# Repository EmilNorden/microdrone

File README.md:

# microdrone

## Controller dev kit

ESP32-S3-Wroom-1-n8r8\
Datasheet: https://www.espressif.com/sites/default/files/documentation/esp32-s3-wroom-1_wroom-1u_datasheet_en.pdf \
Hardware ref: https://docs.espressif.com/projects/esp-dev-kits/en/latest/esp32s3/esp32-s3-devkitc-1/user_guide_v1.1.html#hardware-reference \
Power: 3.0-3.6V\
Rust dev on ESP32: https://docs.espressif.com/projects/rust/book/

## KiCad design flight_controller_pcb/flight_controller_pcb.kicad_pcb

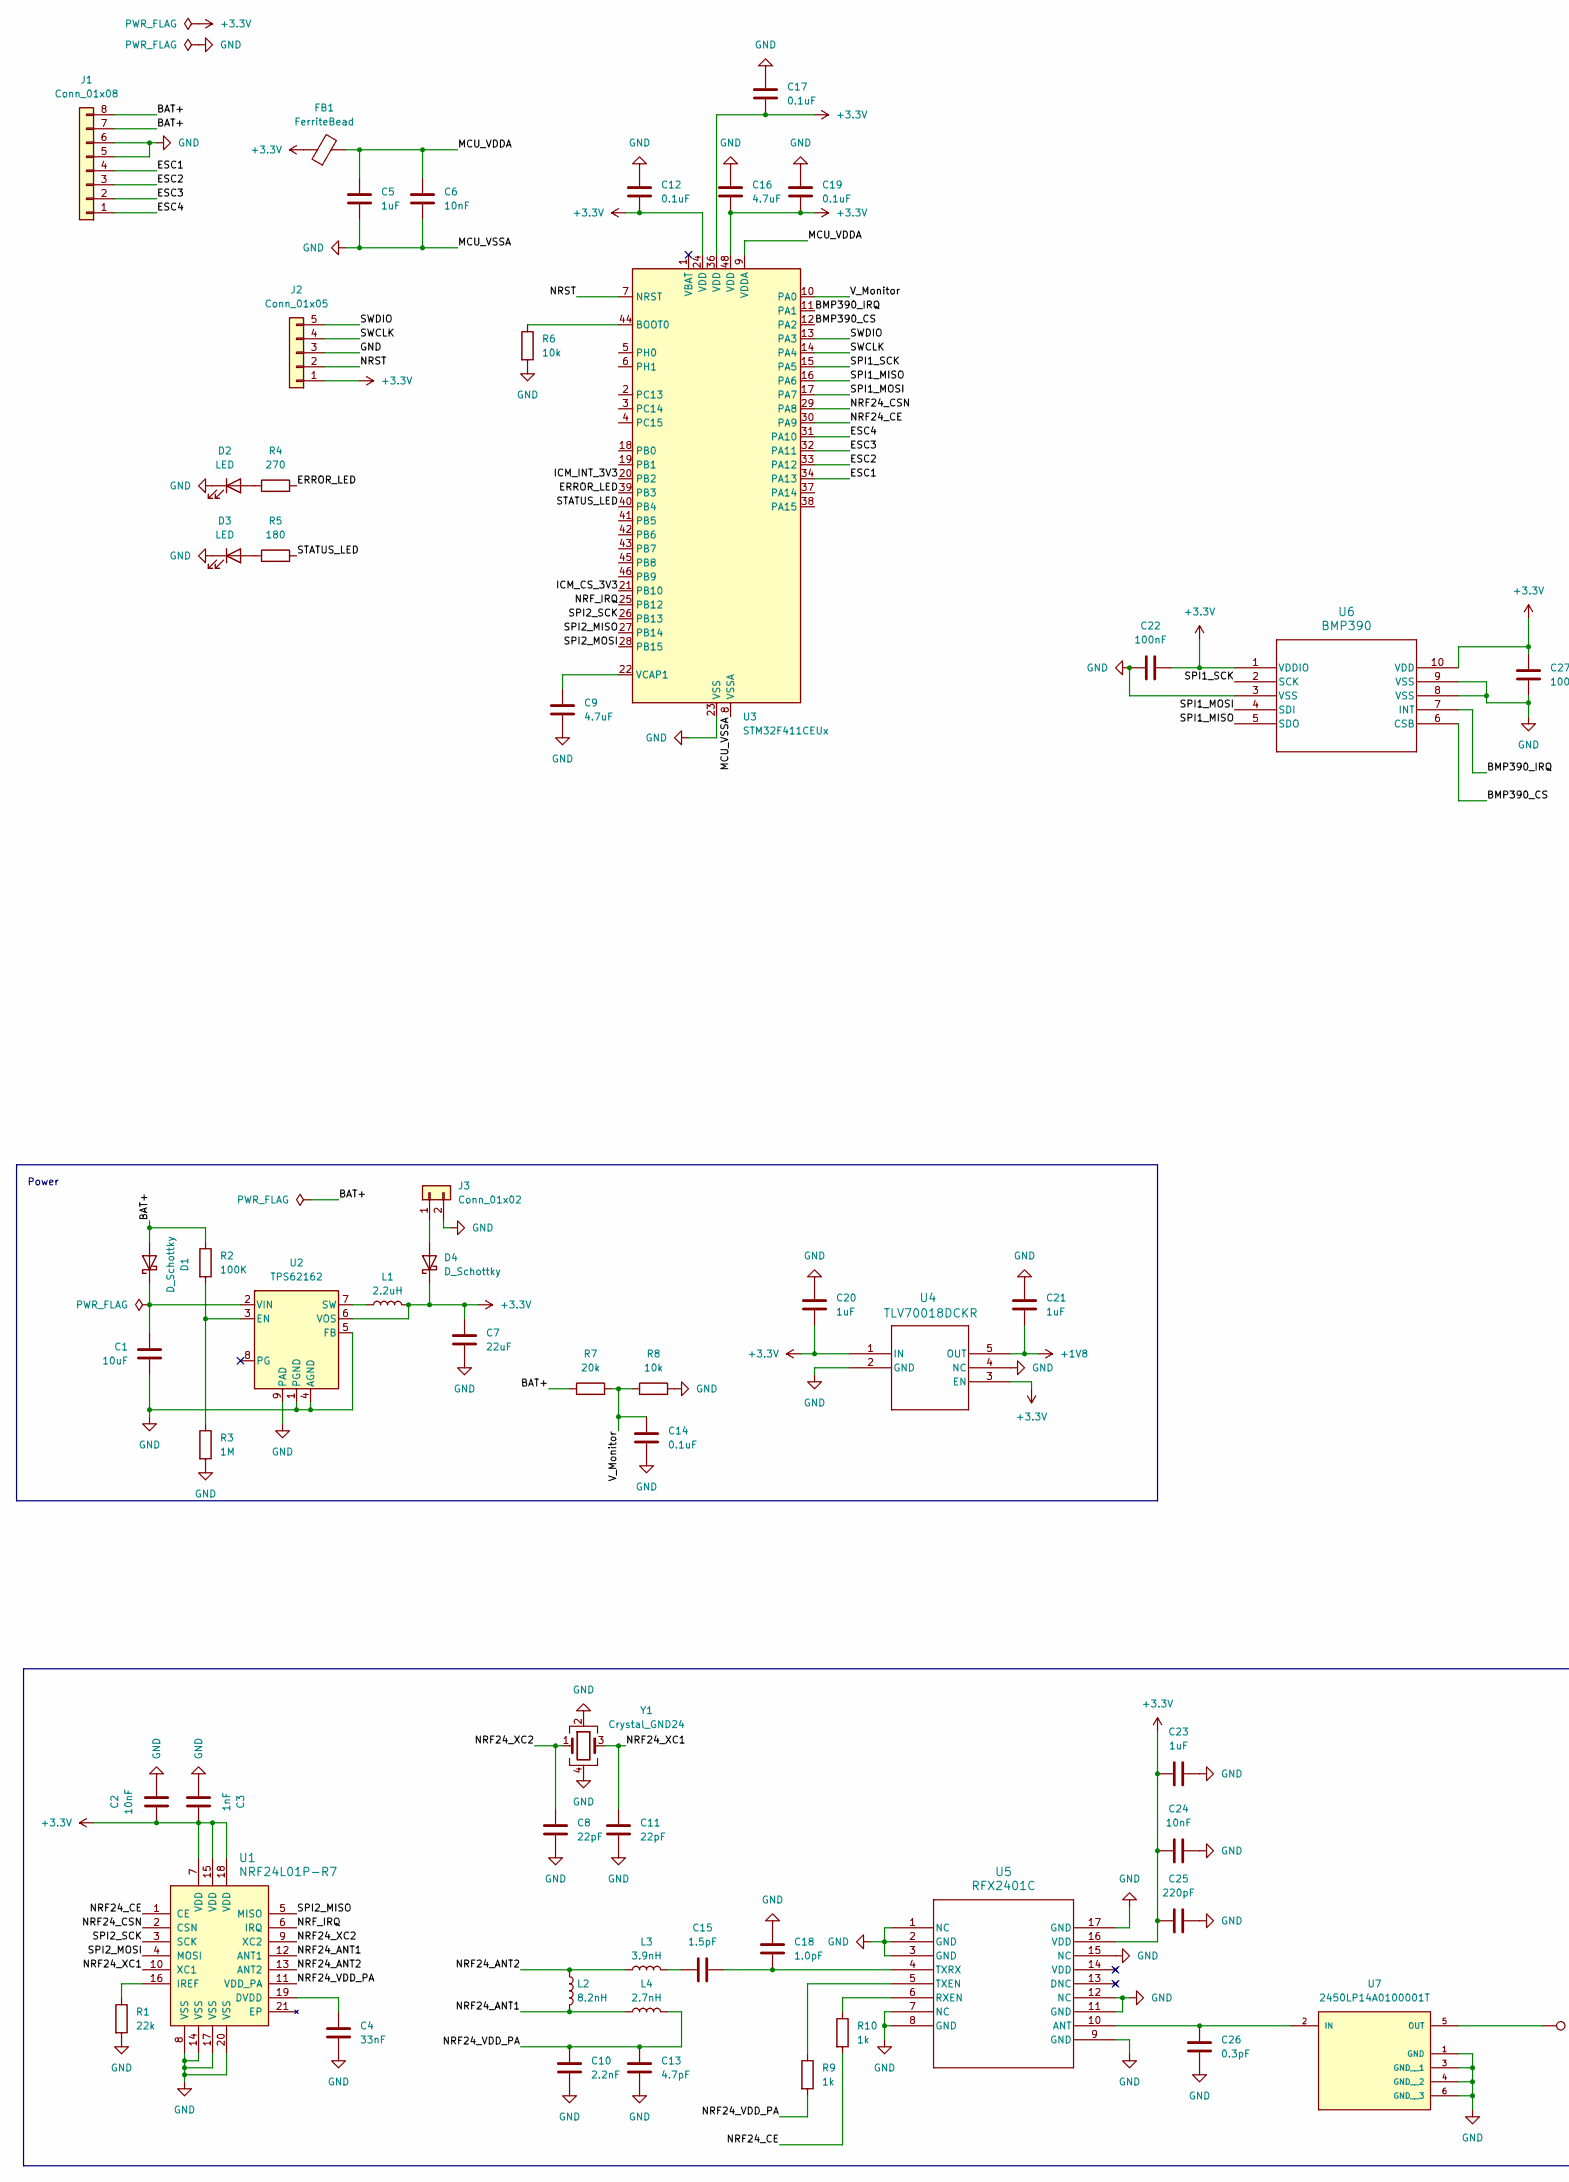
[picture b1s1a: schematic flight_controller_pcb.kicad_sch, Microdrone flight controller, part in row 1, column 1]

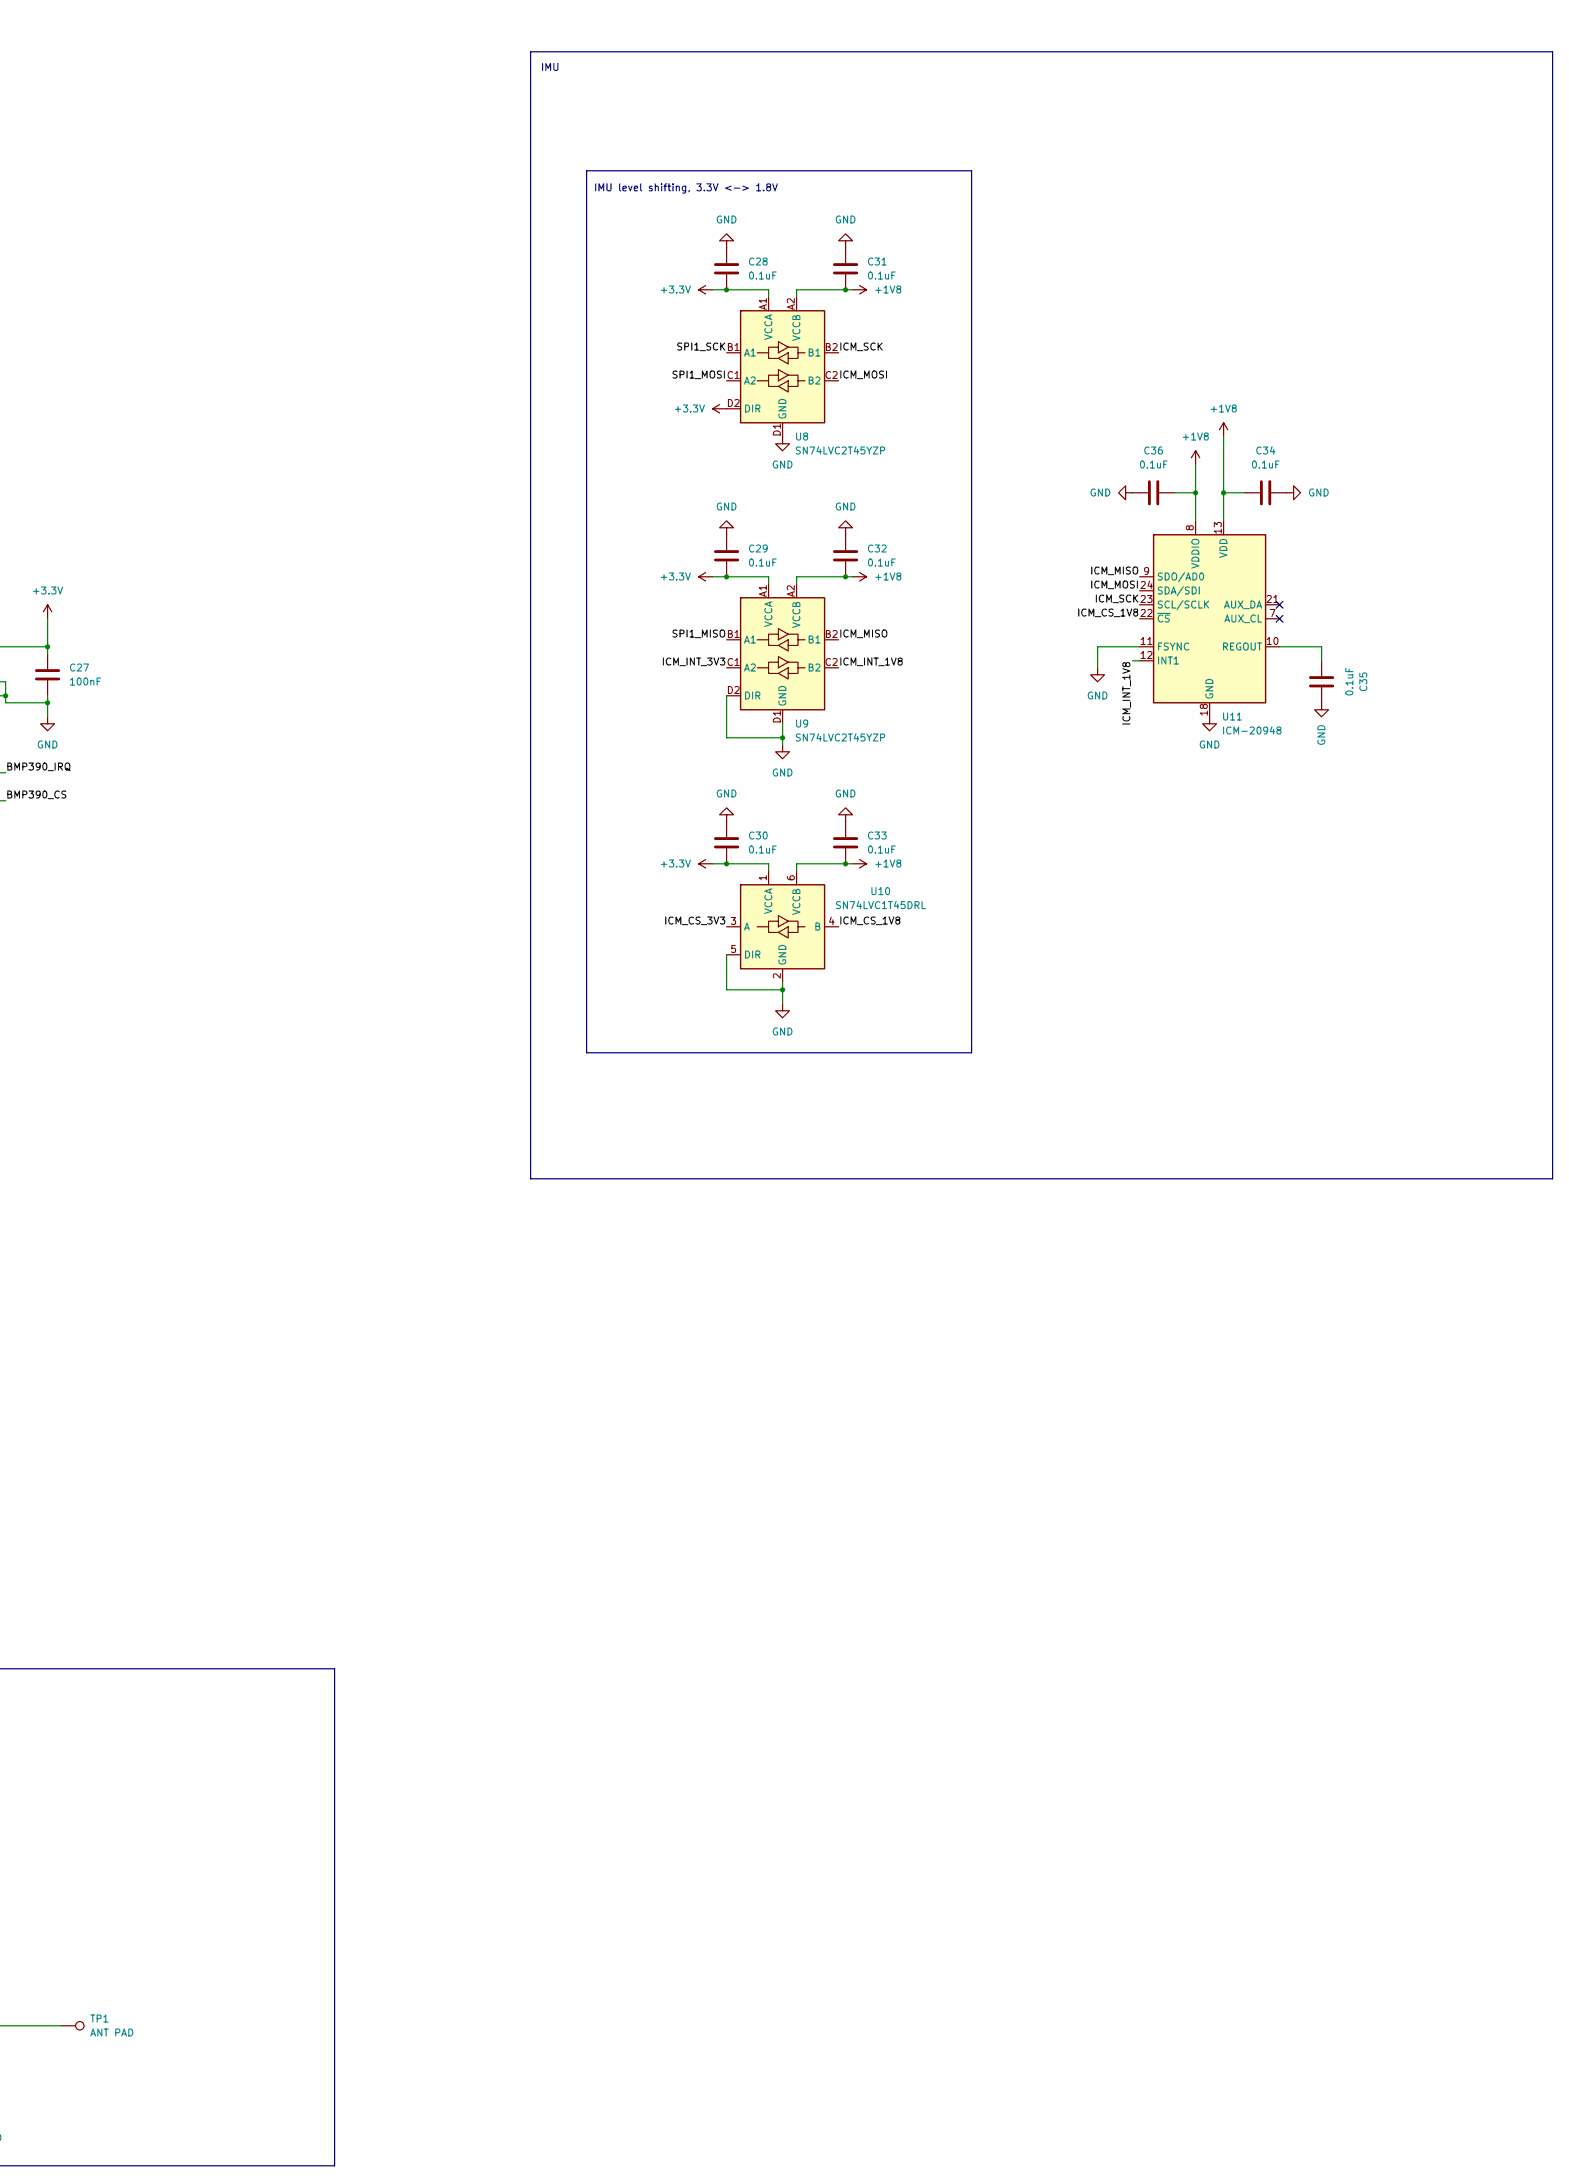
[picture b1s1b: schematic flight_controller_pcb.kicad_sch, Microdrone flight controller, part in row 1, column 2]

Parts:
C1: 10uF; C_0603_1608Metric
C2, C6: 10nF; C_0402_1005Metric
C3: 1nF; C_0402_1005Metric
C4: 33nF; C_0402_1005Metric
C5, C20, C21, C23: 1uF; C_0402_1005Metric
C7: 22uF; C_0805_2012Metric
C8, C11: 22pF; C_0402_1005Metric
C9: 4.7uF; C_0603_1608Metric
C10: 2.2nF; C_0402_1005Metric
C12, C14, C17, C19, C28, C29, C30, C31, C32, C33: 0.1uF; C_0402_1005Metric
C13: 4.7pF; C_0402_1005Metric
C15: 1.5pF; C_0402_1005Metric
C16: 4.7uF; C_0603_1608Metric; LCSC C107368
C18: 1.0pF; C_0402_1005Metric
C22, C27: 100nF; C_0402_1005Metric
C24: 10nF; C_0603_1608Metric
C25: 220pF; C_0402_1005Metric
C26: 0.3pF; C_0201_0603Metric
C34, C35, C36: 0.1uF; C_0402_1005Metric; LCSC C1525
D1: D_Schottky; D_SOD-323
D2, D3: LED; LED_0402_1005Metric
D4: D_Schottky; Diode_SMD_SOD-723
FB1: FerriteBead; L_0603_1608Metric; LCSC C1002
J1: Conn_01x08; JST_SH_ZX-SH1.0-8PWT; LCSC C7430450
J2: Conn_01x05; PinHeader_1x05_P2.54mm_Horizontal
J3: Conn_01x02; PinHeader_1x02_P2.54mm_Horizontal
L1: 2.2uH; Inductor_Coilcraft_XFL3012-222MEC
L2: 8.2nH; L_0201_0603Metric
L3: 3.9nH; L_0201_0603Metric
L4: 2.7nH; L_0201_0603Metric
R1: 22k; R_0402_1005Metric
R2: 100K; R_0402_1005Metric
R3: 1M; R_0402_1005Metric
R4: 270; R_0402_1005Metric
R5: 180; R_0402_1005Metric
R6, R8: 10k; R_0402_1005Metric
R7: 20k; R_0402_1005Metric
R9, R10: 1k; R_0402_1005Metric
TP1: ANT PAD; TestPoint_Pad_3.0x3.0mm
U1: NRF24L01P-R7; QFN-20-1EP_4x4mm_RevA; MPN NRF24L01P-R7; Digi-Key_PN 1490-1033-1-ND
U2: TPS62162; WSON-8-1EP_2x2mm_P0.5mm_EP0.9x1.6mm_ThermalVias
U3: STM32F411CEUx; QFN-48-1EP_7x7mm_P0.5mm_EP5.6x5.6mm
U4: TLV70018DCKR; DCK5
U5: RFX2401C; RFX2401C_SKY
U6: BMP390; 10LGA_2X2X0p75_BOS
U7: 2450LP14A0100001T; ICCAF50P160X80X70-6N; PARTREV 06/23/03
U8, U9: SN74LVC2T45YZP; Texas_DSBGA-8_0.9x1.9mm_Layout2x4_P0.5mm
U10: SN74LVC1T45DRL; SOT-563
U11: ICM-20948; InvenSense_QFN-24_3x3mm_P0.4mm
Y1: Crystal_GND24; Crystal_SMD_3225-4Pin_3.2x2.5mm

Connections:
+1V8: C21.2, C31.2, C32.2, C33.2, C34.1, C36.2, U4.5 (OUT), U8.A2 (VCCB), U9.A2 (VCCB), U10.6 (VCCB), U11.8 (VDDIO), U11.13 (VDD)
+3.3V: C2.1, C3.1, C7.1, C12.1, C16.1, C17.1, C19.1, C20.2, C22.2, C23.1, C24.1, C25.1, C27.1, C28.2, C29.2, C30.2, D4.1 (K), FB1.1, J2.1, L1.2, U1.7 (VDD), U1.15 (VDD), U1.18 (VDD), U2.6 (VOS), U3.24 (VDD), U3.36 (VDD), U3.48 (VDD), U4.1 (IN), U4.3 (EN), U5.16 (VDD), U6.1 (VDDIO), U6.10 (VDD), U8.A1 (VCCA), U8.D2 (DIR), U9.A1 (VCCA), U10.1 (VCCA)
/BAT+: D1.2 (A), J1.7, J1.8, R2.1, R7.1
/BMP390_CS: U3.12 (PA2), U6.6 (CSB)
/BMP390_IRQ: U3.11 (PA1), U6.7 (INT)
/ERROR_LED: R4.2, U3.39 (PB3)
/ESC1: J1.4, U3.34 (PA13)
/ESC2: J1.3, U3.33 (PA12)
/ESC3: J1.2, U3.32 (PA11)
/ESC4: J1.1, U3.31 (PA10)
/ICM_CS_1V8: U10.4 (B), U11.22 (~CS)
/ICM_CS_3V3: U3.21 (PB10), U10.3 (A)
/ICM_INT_1V8: U9.C2 (B2), U11.12 (INT1)
/ICM_INT_3V3: U3.20 (PB2), U9.C1 (A2)
/ICM_MISO: U9.B2 (B1), U11.9 (SDO/AD0)
/ICM_MOSI: U8.C2 (B2), U11.24 (SDA/SDI)
/ICM_SCK: U8.B2 (B1), U11.23 (SCL/SCLK)
/MCU_VDDA: C5.1, C6.1, FB1.2, U3.9 (VDDA)
/NRF24_ANT1: L2.2, L4.1, U1.12 (ANT1)
/NRF24_ANT2: L2.1, L3.1, U1.13 (ANT2)
/NRF24_CE: R10.2, U1.1 (CE), U3.30 (PA9)
/NRF24_CSN: U1.2 (CSN), U3.29 (PA8)
/NRF24_VDD_PA: C10.1, C13.1, L4.2, R9.2, U1.11 (VDD_PA)
/NRF24_XC1: C11.1, U1.10 (XC1), Y1.3
/NRF24_XC2: C8.1, U1.9 (XC2), Y1.1
/NRF_IRQ: U1.6 (IRQ), U3.25 (PB12)
/NRST: J2.2, U3.7 (NRST)
/SPI1_MISO: U3.16 (PA6), U6.5 (SDO), U9.B1 (A1)
/SPI1_MOSI: U3.17 (PA7), U6.4 (SDI), U8.C1 (A2)
/SPI1_SCK: U3.15 (PA5), U6.2 (SCK), U8.B1 (A1)
/SPI2_MISO: U1.5 (MISO), U3.27 (PB14)
/SPI2_MOSI: U1.4 (MOSI), U3.28 (PB15)
/SPI2_SCK: U1.3 (SCK), U3.26 (PB13)
/STATUS_LED: R5.2, U3.40 (PB4)
/SWCLK: J2.4, U3.14 (PA4)
/SWDIO: J2.5, U3.13 (PA3)
/V_Monitor: C14.2, R7.2, R8.1, U3.10 (PA0)
GND: C1.2, C2.2, C3.2, C4.1, C5.2, C6.2, C7.2, C8.2, C9.1, C10.2, C11.2, C12.2, C13.2, C14.1, C16.2, C17.2, C18.1, C19.2, C20.1, C21.1, C22.1, C23.2, C24.2, C25.2, C26.2, C27.2, C28.1, C29.1, C30.1, C31.1, C32.1, C33.1, C34.2, C35.2, C36.1, D2.1 (K), D3.1 (K), J1.5, J1.6, J2.3, J3.2, R1.2, R3.2, R6.2, R8.2, U1.8 (VSS), U1.14 (VSS), U1.17 (VSS), U1.20 (VSS), U2.1 (PGND), U2.4 (AGND), U2.5 (FB), U2.9 (PAD), U3.8 (VSSA), U3.23 (VSS), U3.35 (VSS), U3.47 (VSS), U3.49 (VSS), U4.2 (GND), U4.4 (NC), U5.1 (NC), U5.2 (GND), U5.3 (GND), U5.7 (NC), U5.8 (GND), U5.9 (GND), U5.11 (GND), U5.12 (NC), U5.15 (NC), U5.17 (GND), U6.3 (VSS), U6.8 (VSS), U6.9 (VSS), U7.1 (GND), U7.3 (GND__1), U7.4 (GND__2), U7.6 (GND__3), U8.D1 (GND), U9.D1 (GND), U9.D2 (DIR), U10.2 (GND), U10.5 (DIR), U11.11 (FSYNC), U11.18 (GND), U11.20 (GND), Y1.2, Y1.4
unnamed: C15.1, L3.2
unnamed: C1.1, D1.1 (K), U2.2 (VIN)
unnamed: D2.2 (A), R4.1
unnamed: D3.2 (A), R5.1
unnamed: D4.2 (A), J3.1
unnamed: C4.2, U1.19 (DVDD)
unnamed: R1.1, U1.16 (IREF)
unnamed: R2.2, R3.1, U2.3 (EN)
unnamed: L1.1, U2.7 (SW)
unnamed: R6.1, U3.44 (BOOT0)
unnamed: C9.2, U3.22 (VCAP1)
unnamed: C26.1, U5.10 (ANT), U7.2 (IN)
unnamed: R10.1, U5.6 (RXEN)
unnamed: R9.1, U5.5 (TXEN)
unnamed: C15.2, C18.2, U5.4 (TXRX)
unnamed: TP1.1, U7.5 (OUT)
unnamed: C35.1, U11.10 (REGOUT)

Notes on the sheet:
IMU
IMU level shifting, 3.3V <-> 1.8V
Power

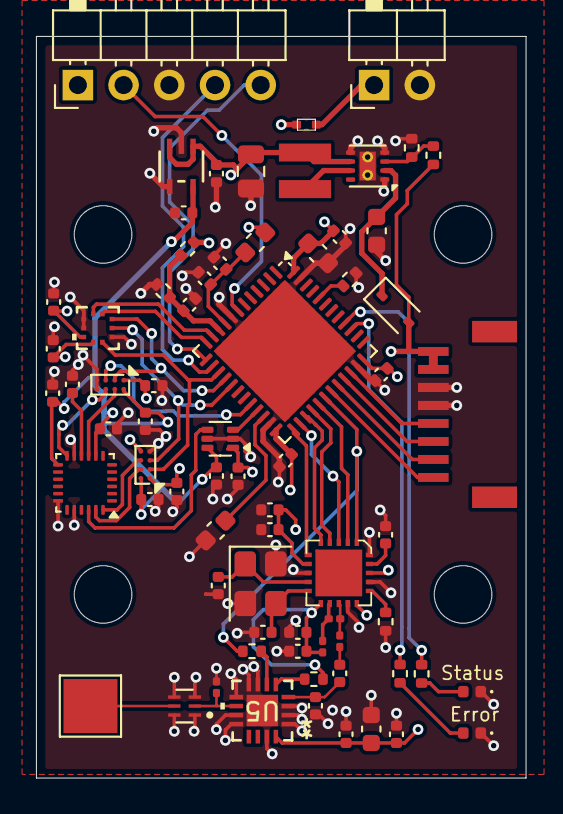
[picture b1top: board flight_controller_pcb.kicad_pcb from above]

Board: 4 copper layers, 27.2 x 41.2 mm, 71 parts (0 on the bottom side), 55 nets.

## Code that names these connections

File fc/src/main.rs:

#![no_std]
#![no_main]
mod bms;
mod env;
mod radio;
mod signal;

use crate::signal::{
    altitude_signal, drone_battery_level_signal, drone_battery_status_signal, new_drone_battery_level_signal_emitter,
    new_drone_battery_status_signal_emitter, BatteryStatus,
};
use defmt::*;
use embassy_embedded_hal::shared_bus::asynch::spi::SpiDevice;
use embassy_executor::Spawner;
use embassy_futures::select::{select, Either};
use embassy_stm32::adc::{Adc, AdcChannel, VREF_CALIB_MV};
use embassy_stm32::exti::ExtiInput;
use embassy_stm32::gpio::{Level, Output, Pull, Speed};
use embassy_stm32::mode::Async;
use embassy_stm32::peripherals::ADC1;
use embassy_stm32::spi::{Config, Spi};
use embassy_stm32::time::Hertz;
use embassy_sync::blocking_mutex::raw::NoopRawMutex;
use embassy_sync::mutex::Mutex;
use embassy_time::{Duration, Timer};
use fc_common::SignalBase;
use static_cell::StaticCell;
use {defmt_rtt as _, panic_probe as _};

static SPI_BUS: StaticCell<Mutex<NoopRawMutex, Spi<Async>>> = StaticCell::new();

fn read_calibrated_vdda(adc: &mut Adc<ADC1>) -> u32 {
    let mut vref = adc.enable_vrefint();

    let vref_raw = adc.blocking_read(&mut vref);

    let vref_cal = unsafe { core::ptr::read_volatile(0x1FFF_7A2A as *const u16) };

    VREF_CALIB_MV * (vref_cal as u32) / (vref_raw as u32)
}

async fn timeout<A: Future>(duration: Duration, awaitable: A) -> Option<A::Output> {
    match select(Timer::after(duration), awaitable).await {
        Either::First(_) => None,
        Either::Second(x) => Some(x),
    }
}

async fn battery_power_on_self_test() {
    let mut battery_status = drone_battery_status_signal();
    let battery_status = timeout(Duration::from_secs(1), battery_status.next_value()).await;

    match battery_status {
        None => defmt::panic!("Battery status timeout"),
        Some(BatteryStatus::Critical) => defmt::panic!("Battery level critical."),
        Some(_) => {}
    };
}

#[embassy_executor::main]
async fn main(spawner: Spawner) {
    let p = embassy_stm32::init(Default::default());
    info!("Flight controller starting.");

    // Start-up BMS (Battery Management Subsystem) first
    spawner
        .spawn(bms::run(
            p.PA0.degrade_adc(),
            Adc::new(p.ADC1),
            new_drone_battery_level_signal_emitter(),
            new_drone_battery_status_signal_emitter(),
        ))
        .unwrap();

    // Halt start-up if battery level is critical
    battery_power_on_self_test().await;

    // Setup SPI
    let mut spi_config = Config::default();
    spi_config.frequency = Hertz(1_000_000);
    let spi = Spi::new(
        p.SPI1, p.PA5, p.PA7, p.PA6, p.DMA2_CH3, p.DMA2_CH2, spi_config,
    );
    let spi_bus = Mutex::new(spi);
    let spi_bus = SPI_BUS.init(spi_bus);

    // NRF24L01+
    let radio_cs = Output::new(p.PB13, Level::High, Speed::Low);
    let radio_device = SpiDevice::new(spi_bus, radio_cs);

    let radio_ce = Output::new(p.PB12, Level::High, Speed::Low);
    let radio_irq = ExtiInput::new(p.PB1, p.EXTI1, Pull::Up);
    spawner
        .spawn(radio::run(
            radio_device,
            radio_ce,
            radio_irq,
            drone_battery_level_signal(),
            altitude_signal(),
        ))
        .unwrap();

    let bmp390_cs = Output::new(p.PB14, Level::High, Speed::Low);
    let bmp390_device = SpiDevice::new(spi_bus, bmp390_cs);
    let bmp390_irq = ExtiInput::new(p.PB6, p.EXTI6, Pull::Up);

    spawner.spawn(env::run(bmp390_device, bmp390_irq)).unwrap();
    /*
    let r = adc.blocking_read(&mut battery);

    let mut buf = [0u16; 32];

    // Enable DMA2 clock
    embassy_stm32::pac::RCC.ahb1enr().modify(|w| w.set_dma2en(true));

    // Disable stream
    embassy_stm32::pac::DMA2.st(0).cr().modify(|w| w.set_en(false));
    while embassy_stm32::pac::DMA2.st(0).cr().read().en() {}

    embassy_stm32::pac::DMA2.ifcr(0).write(|w| {
        w.set_tcif(0, true);
        w.set_htif(0, true);
        w.set_teif(0, true);
        w.set_dmeif(0, true);
        w.set_feif(0, true);
    });*/

    // Set up TIM3
    //embassy_stm32::pac::RCC.apb1enr().modify(|w| w.set_tim3en(true));
    /*
        let timer = embassy_stm32::timer::low_level::Timer::new(p.TIM3);
        timer.set_frequency(Hertz(400));
        // Set TRGO to trigger on update event. This has no API in the embassy low level driver, so I have to go through PAC.
        embassy_stm32::pac::TIM3.cr2().modify(|w| w.set_mms(Mms::UPDATE));
        timer.start();
    */

    info!("Flight controller started!");
    core::future::pending::<()>().await;
}

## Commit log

2025-07-30 initial commit of controller
2025-08-05 initial commit of FC pcb
2025-08-05 assigned several footprints in FC schema
2025-08-05 gamepad connectivity + display updates
2025-08-08 Implemented test communication between two nRF24 modules
2025-08-08 Started work to replace mpu-6500 with icm-20948
2025-08-08 Added nRF24L01+ and BMP390 datasheets
2025-08-10 initial commit of flight controller crate
2025-08-11 tons of work on radio communication between controller and fc
2025-08-31 send controller input to FC
2025-09-02 changed to local version of nrf24-rs for async support etc
2025-09-02 Adde interrupt line for bmp390
2025-09-02 updated usage of nrf24 after local changes to repo
2025-09-02 Removed .DS_Store files
2025-09-03 added rustfmt.toml
2025-09-12 Moved telemetry stuff into fc-common
2025-09-12 Rewrote telemetry + added crude BMS subsystem
2025-09-12 Refactored telemetry + changed ACK data
2025-09-15 ALOT of work on the PCB
2025-09-20 alot of work around internal signaling and RF robustness
2025-09-20 Display drone battery level on display
2025-09-24 Some work on the radio
2025-09-24 Made each distinct signal its own type instead of a type alias
2025-09-25 pcb routing
2025-09-25 added datasheets for esp32 and stm32 mcu + technical reference for stm32
2025-09-25 added .DS_Store in gitignore
2025-09-25 split peripherals up into SPI2/SPI3 since ssd1351 driver does currently not support async
2025-09-26 moved interrupt await to *before* calculating link score
2025-10-01 alot of work on pcb layout
2025-10-03 routing work
2025-10-03 more routing
2025-10-04 finished most of the traces
2025-10-05 added antenna lip

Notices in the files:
flight_controller_pcb/flight_controller_pcb.kicad_pcb:
creativecommons.org/licenses/by/4.0
License: CC BY 4.0
